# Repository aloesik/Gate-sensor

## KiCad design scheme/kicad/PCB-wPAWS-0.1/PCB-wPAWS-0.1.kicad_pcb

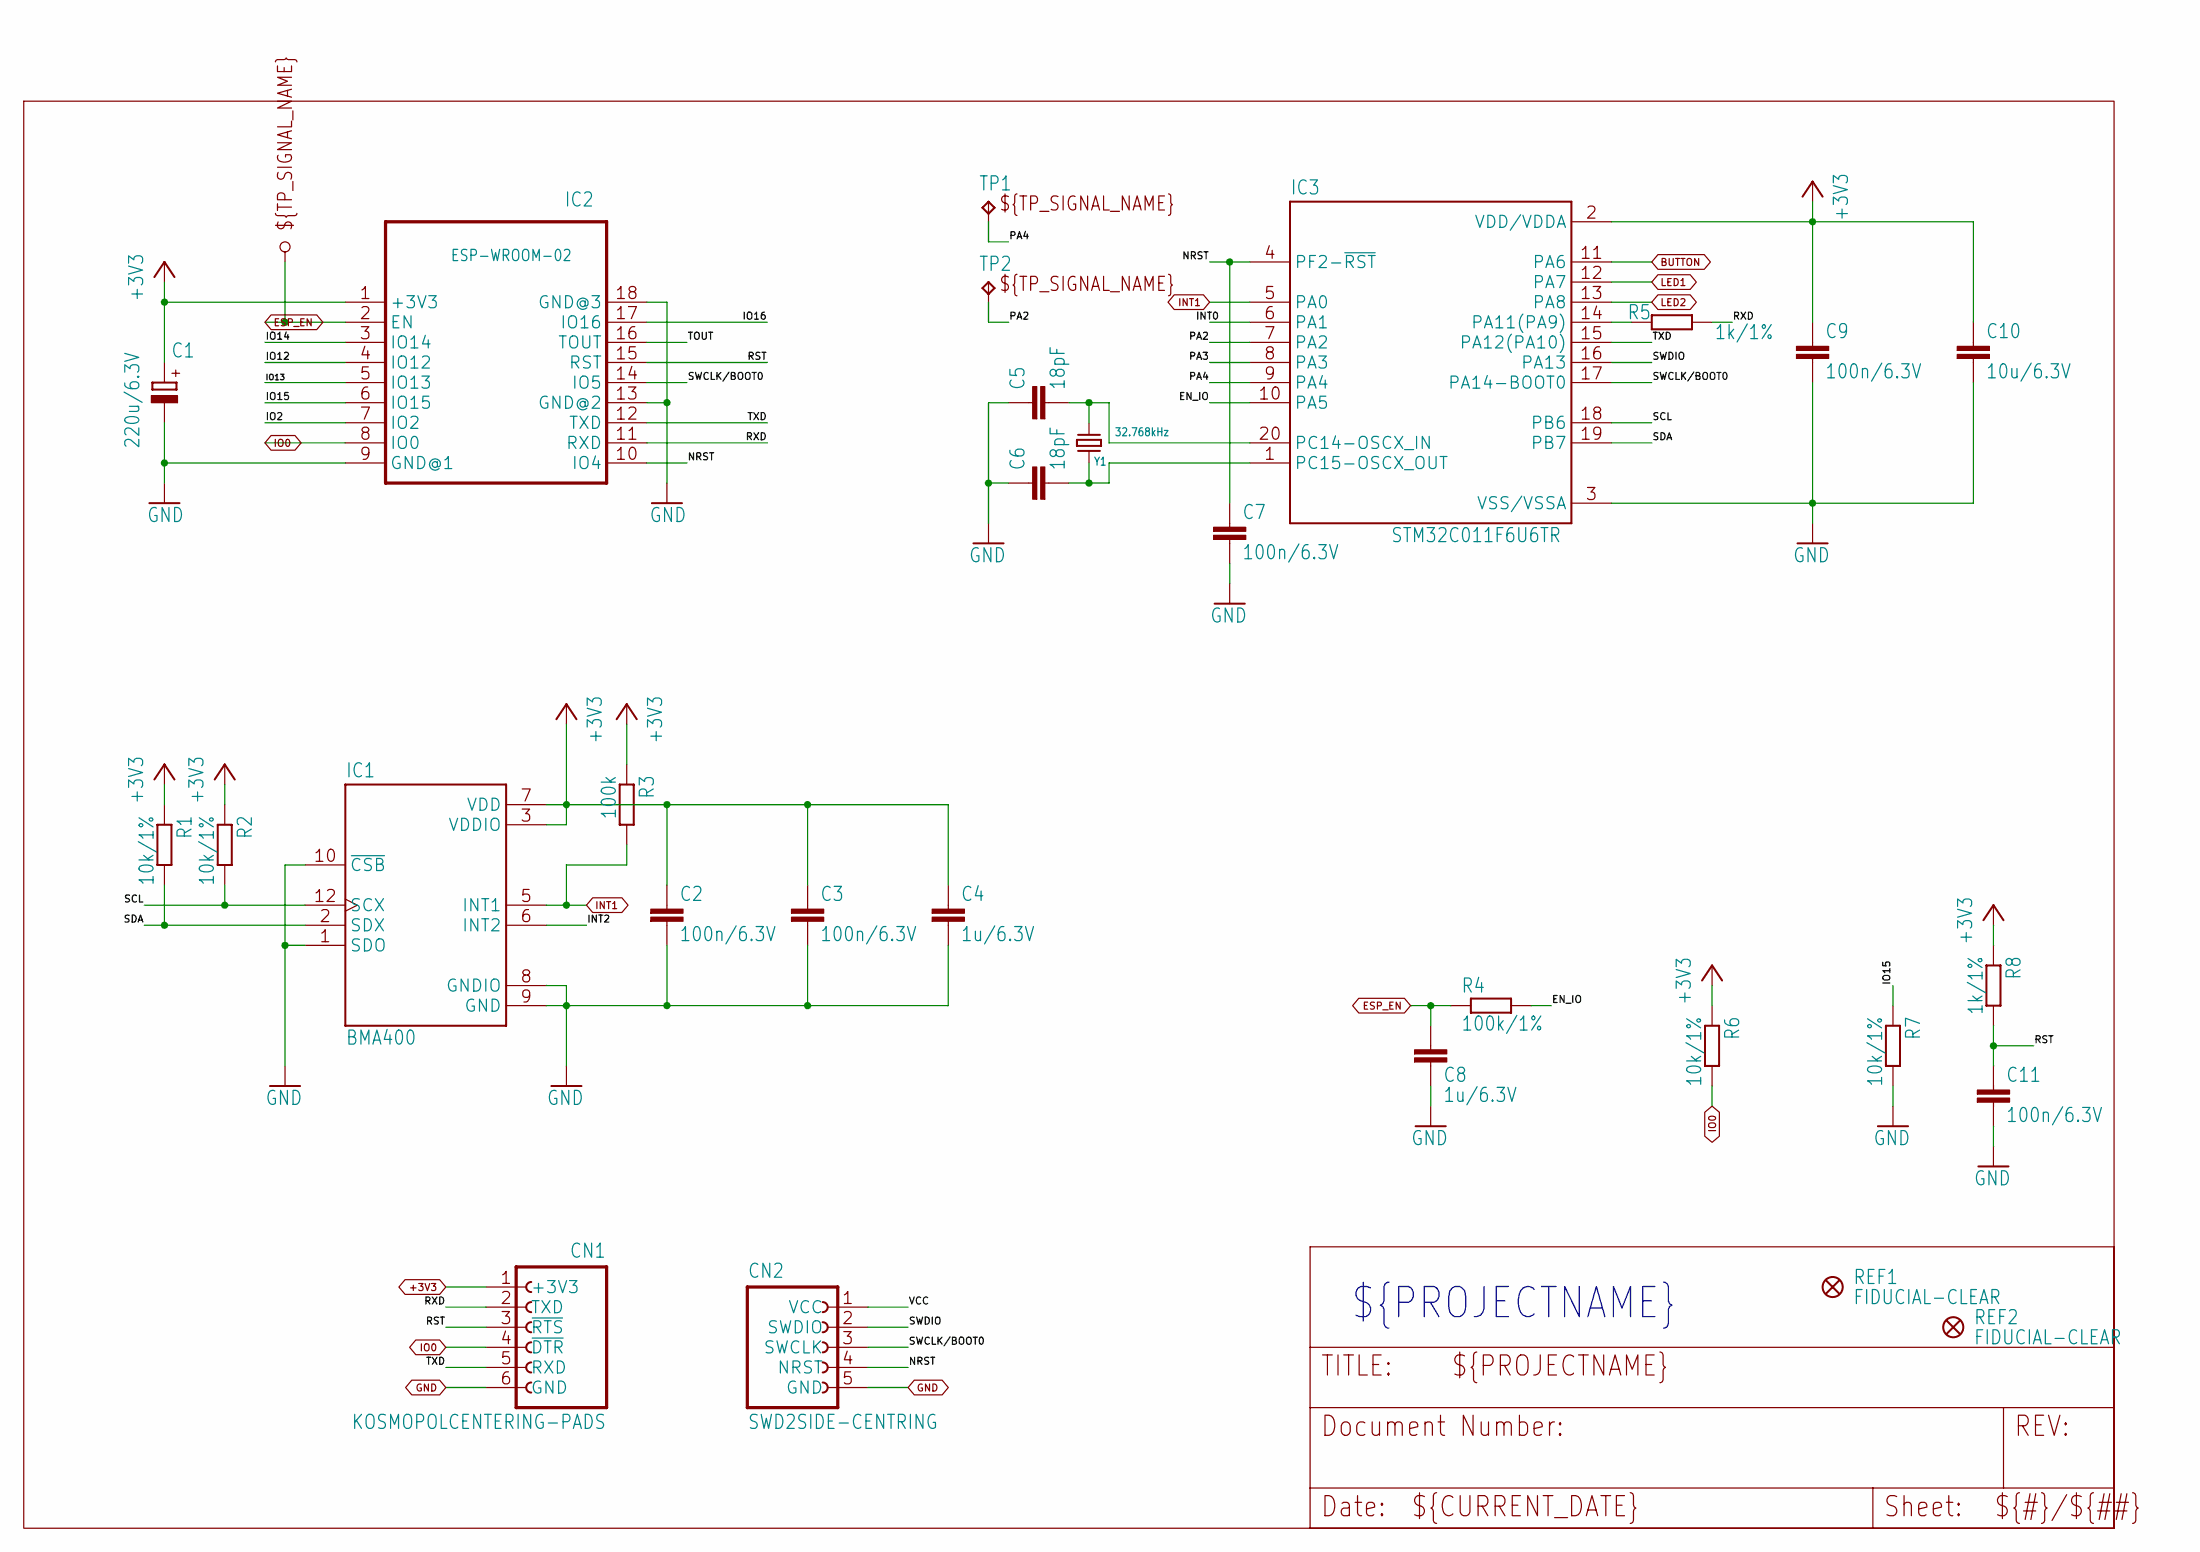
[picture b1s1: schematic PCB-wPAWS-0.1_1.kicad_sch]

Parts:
C1: 220u/6.3V; SMC_C
C2, C3, C7, C9, C11: 100n/6.3V; C0402
C4, C8: 1u/6.3V; C0402
C5, C6: 18pF; C0402
C10: 10u/6.3V; C0402
CN1: KOSMOPOLCENTERING-PADS; 6P-2.54-CENTERING-HOLE-PAD
CN2: SWD2SIDE-CENTRING; FE05W-SWD-CP
IC1: BMA400; XDCR_BMA400
IC2: ESP-WROOM-02; MODULE
IC3: STM32C011F6U6TR; IC_STM32C011F6U6TR
JP1: PINHD-1X1; 1X01
R1, R2, R6, R7: 10k/1%; R0402
R3: 100k; R0402
R4: 100k/1%; R0402
R5, R8: 1k/1%; R0402
REF1, REF2: FIDUCIAL-CLEAR; FIDUCIAL-ANDPOL
TP1, TP2: TPB1,27; B1,27
Y1: 32.768kHz; WE-XTAL_CFPX-217

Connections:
+3V3: C1.+, C2.1, C3.1, C4.1, C9.1, C10.1, CN1.1 (+3V3), IC1.3 (VDDIO), IC1.7 (VDD), IC2.1 (+3V3), IC3.2 (VDD/VDDA), R1.1, R2.1, R3.1, R6.1, R8.1; also elsewhere on the board
BUTTON: IC3.11 (PA6); also elsewhere on the board
EN_IO: IC3.10 (PA5), R4.2
ESP_EN: C8.1, IC2.2 (EN), JP1.1, R4.1; also elsewhere on the board
GND: C1.-, C2.2, C3.2, C4.2, C5.1, C6.1, C7.2, C8.2, C9.2, C10.2, C11.2, CN1.6 (GND), CN2.5 (GND), IC1.1 (SDO), IC1.8 (GNDIO), IC1.9 (GND), IC1.10 (~CSB), IC2.9 (GND@1), IC2.13 (GND@2), IC2.18 (GND@3), IC3.3 (VSS/VSSA), R7.2; also elsewhere on the board
INT0: IC3.6 (PA1)
INT1: IC1.5 (INT1), IC3.5 (PA0), R3.2; also elsewhere on the board
INT2: IC1.6 (INT2)
IO0: CN1.4 (~DTR), IC2.8 (IO0), R6.2; also elsewhere on the board
IO2: IC2.7 (IO2)
IO12: IC2.4 (IO12)
IO13: IC2.5 (IO13)
IO14: IC2.3 (IO14)
IO15: IC2.6 (IO15), R7.1
IO16: IC2.17 (IO16)
LED1: IC3.12 (PA7); also elsewhere on the board
LED2: IC3.13 (PA8); also elsewhere on the board
unnamed: C6.2, IC3.1 (PC15-OSCX_OUT), Y1.1
NRST: C7.1, CN2.4 (NRST), IC2.10 (IO4), IC3.4 (PF2-~RST)
PA2: IC3.7 (PA2), TP2.TP
PA3: IC3.8 (PA3)
PA4: IC3.9 (PA4), TP1.TP
PC14-OSCX_IN: C5.2, IC3.20 (PC14-OSCX_IN), Y1.2
RST: C11.1, CN1.3 (~RTS), IC2.15 (RST), R8.2
RXD: CN1.2 (TXD), IC2.11 (RXD), R5.2
SCL: IC1.12 (SCX), IC3.18 (PB6), R2.2
SDA: IC1.2 (SDX), IC3.19 (PB7), R1.2
STM_RXD: IC3.14 (PA11(PA9)), R5.1
SWCLK/BOOT0: CN2.3 (SWCLK), IC2.14 (IO5), IC3.17 (PA14-BOOT0)
SWDIO: CN2.2 (SWDIO), IC3.16 (PA13)
TOUT: IC2.16 (TOUT)
TXD: CN1.5 (RXD), IC2.12 (TXD), IC3.15 (PA12(PA10))
VCC: CN2.1 (VCC)

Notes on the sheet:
${PROJECTNAME}

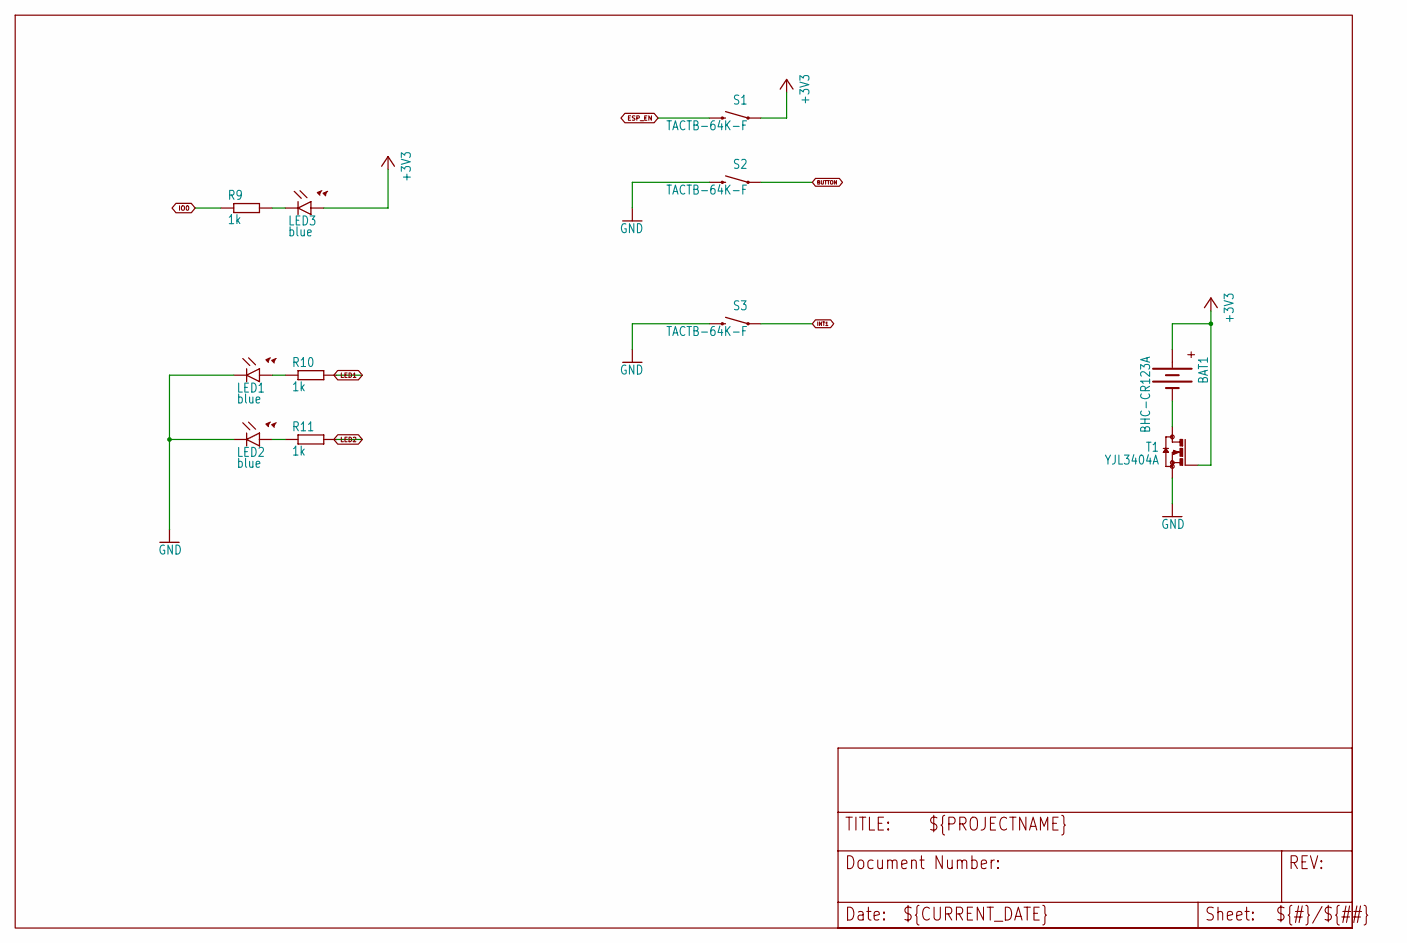
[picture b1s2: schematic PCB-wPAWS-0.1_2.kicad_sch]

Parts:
BAT1: BHC-CR123A
LED1, LED2, LED3: blue; CHIPLED_0603
R9, R10, R11: 1k; R0402
S1, S2, S3: TACTB-64K-F; TACTILE-SWITCH-SMD
T1: YJL3404A; SOT23-R_INFINEON

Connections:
+3V3: BAT1.VCC (+), LED3.A, S1.1, T1.1 (G); also elsewhere on the board
BUTTON: S2.1; also elsewhere on the board
ESP_EN: S1.3 (2); also elsewhere on the board
GND: LED1.C, LED2.C, S2.3 (2), S3.3 (2), T1.2 (S); also elsewhere on the board
INT1: S3.1; also elsewhere on the board
IO0: R9.1; also elsewhere on the board
LED1: R10.2; also elsewhere on the board
LED2: R11.2; also elsewhere on the board
LED3C: LED3.C, R9.2
unnamed: BAT1.GND (-), T1.3 (D)
unnamed: LED2.A, R11.1
unnamed: LED1.A, R10.1

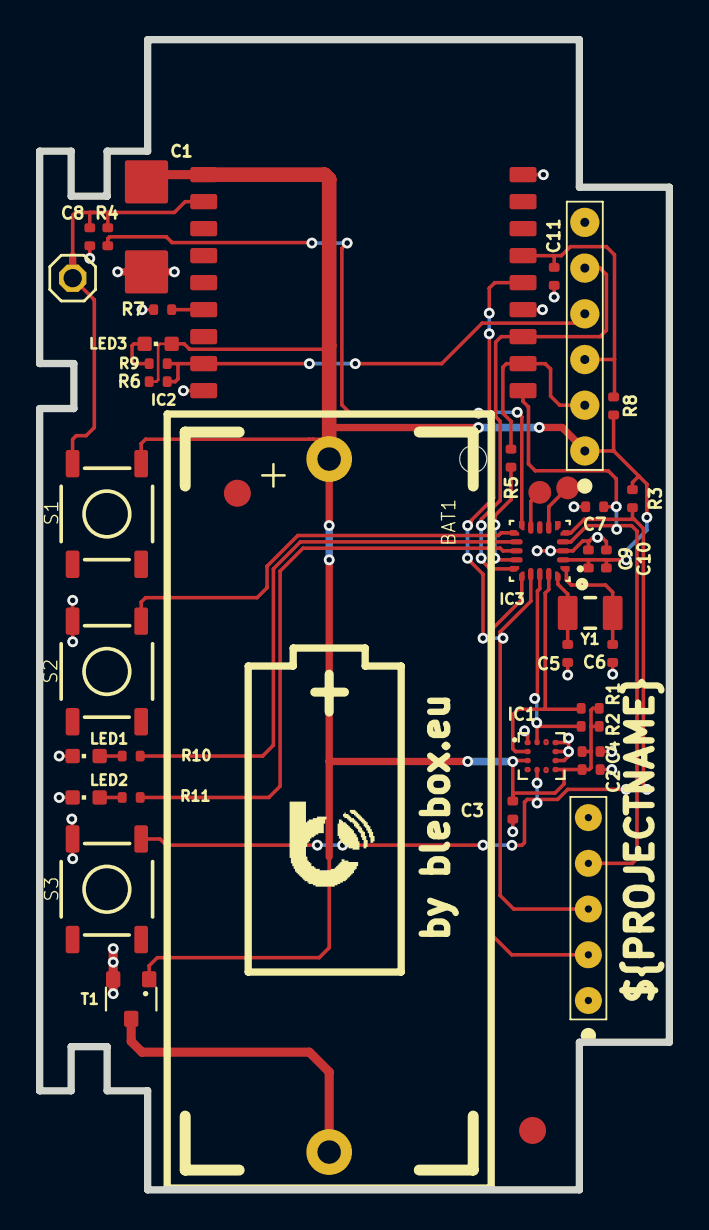
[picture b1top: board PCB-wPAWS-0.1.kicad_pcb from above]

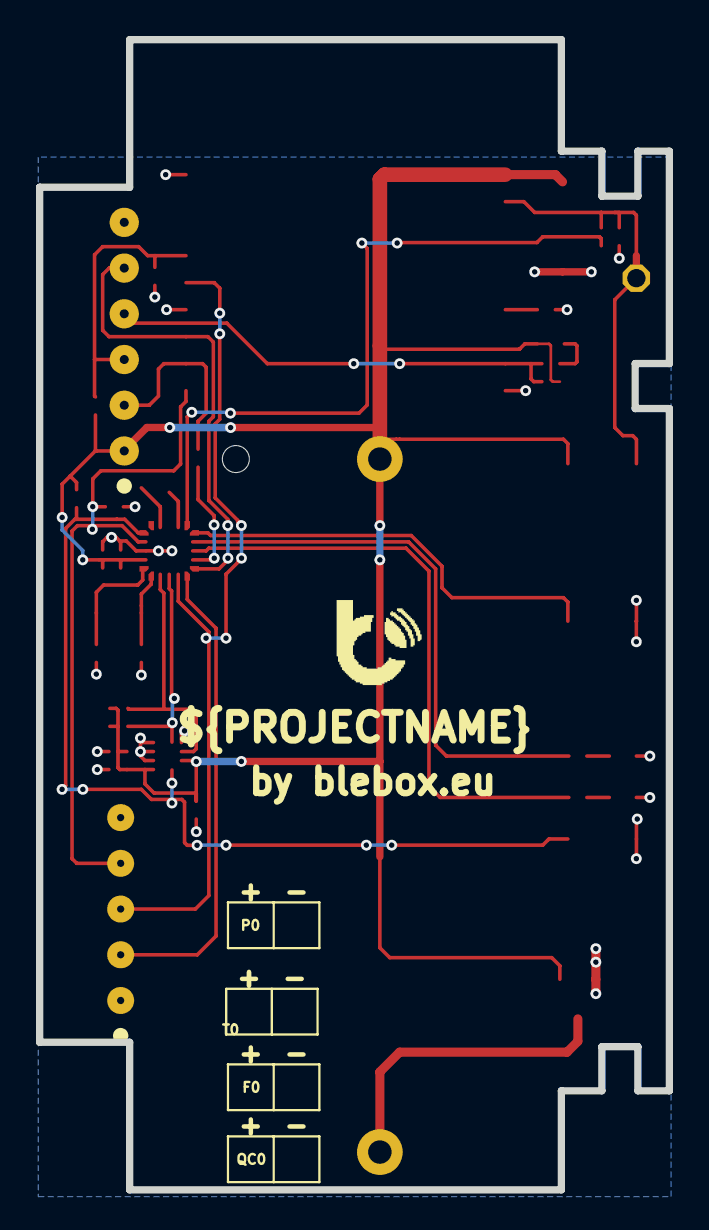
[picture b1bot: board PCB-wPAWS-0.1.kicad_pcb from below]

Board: 2 copper layers, 35.0 x 63.9 mm, 47 parts (5 on the bottom side), 27 nets.

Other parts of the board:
F0: MANUFACTURING-TEST
P0: MANUFACTURING-TEST
QC0: MANUFACTURING-TEST
T0: MANUFACTURING-TEST
U$1, U$4: BLEBOX-LOGO-MEDIUM_26685265

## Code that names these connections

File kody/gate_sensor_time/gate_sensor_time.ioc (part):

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Mcu.Name=STM32C011F(4-6)Ux
Mcu.Package=UFQFPN20
Mcu.UserName=STM32C011F6Ux
PA0.GPIOParameters=GPIO_Label
PA0.GPIO_Label=INT1
PA0.Mode=WakeUp1
PA0.Signal=PWR_WKUP1
PA1.Signal=GPIO_Analog
PA10\ [PA12].Mode=Asynchronous
PA10\ [PA12].Signal=USART1_RX
PA13.Mode=Serial_Wire
PA13.Signal=DEBUG_SWDIO
PA14-BOOT0.Mode=Serial_Wire
PA14-BOOT0.Signal=DEBUG_SWCLK
PA2.Signal=GPIO_Analog
PA3.Signal=GPIO_Analog
PA4.Signal=GPIO_Analog
PA5.GPIOParameters=GPIO_Label
PA5.GPIO_Label=EN_IO
PA5.Signal=GPIO_Output
PA6.GPIOParameters=GPIO_PuPd,GPIO_Label
PA6.GPIO_Label=Button
PA6.GPIO_PuPd=GPIO_PULLUP
PA6.Signal=GPIO_Input
PA7.GPIOParameters=GPIO_Label
PA7.GPIO_Label=LED1
PA7.Signal=GPIO_Output
PA8.GPIOParameters=GPIO_Label
PA8.GPIO_Label=LED2
PA8.Signal=GPIO_Output
PA9\ [PA11].Mode=Asynchronous
PA9\ [PA11].Signal=USART1_TX
PB6.GPIOParameters=GPIO_Pu
PB6.GPIO_Pu=GPIO_PULLUP
PB6.Mode=I2C
PB6.Signal=I2C1_SCL
PB7.GPIOParameters=GPIO_Pu
PB7.GPIO_Pu=GPIO_PULLUP
PB7.Mode=I2C
PB7.Signal=I2C1_SDA
PC14-OSCX_IN\ (PC14).Signal=RCC_OSCX_IN
PC15-OSCX_OUT\ (PC15).Signal=RCC_OSCX_OUT
PF2-NRST.GPIOParameters=GPIO_Label
PF2-NRST.GPIO_Label=NRST
PF2-NRST.Signal=GPIO_Input
RCC.HSE_VALUE=8000000
RCC.SYSCLKFreq_VALUE=3000000
board=custom

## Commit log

2025-07-15 esp communication
2025-07-16 range 0-100 fixed
2025-07-22 modified esp and stm code
2025-07-22 previous
2025-07-22 stop changed to standby
2025-07-22 description update
2025-07-22 send from esp to stm
2025-07-23 data
2025-07-23 data 100 ms
2025-07-24 collect data
2025-07-27 data analysis
2025-07-28 samples gathering
2025-07-28 10 ms data
2025-07-28 10 ms analysis
2025-07-29 fifo bma400
2025-07-30 moving state update
2025-07-31 gate_sensor update
2025-07-31 counting time
2025-08-01 esp-now communication
2025-08-04 start/end of motion data
2025-08-05 counting average
2025-08-05 calculate average
2025-08-07 average change
2025-08-12 low power
